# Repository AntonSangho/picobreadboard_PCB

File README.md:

# 프로젝트명 : 포르쉐 

### Images

# 요구사항 작성을 위한 질문 
- 수집하고자하는 환경데이터: 예) 온도, 습도  
- 휴대가능여부 
- 물리적인 사이즈 : 예) 휴대폰사이즈 , 카드지갑사이즈 
- 사용자가 손으로 제어하는 방식 : 예) 버튼
- 사용자가 동작을 확인하는 형태 : 예) LED, 부저음, 액정디스플레이
- 데이터를 확인하는 시각적인 결과물의 형태 : 예) 로우데이터, 그래프 
- 생각하는 키트의 외관 형태 
- 베터리로 동작하는 경우, 사용가능해야하는 대략적인 시간 
- 제작 수량

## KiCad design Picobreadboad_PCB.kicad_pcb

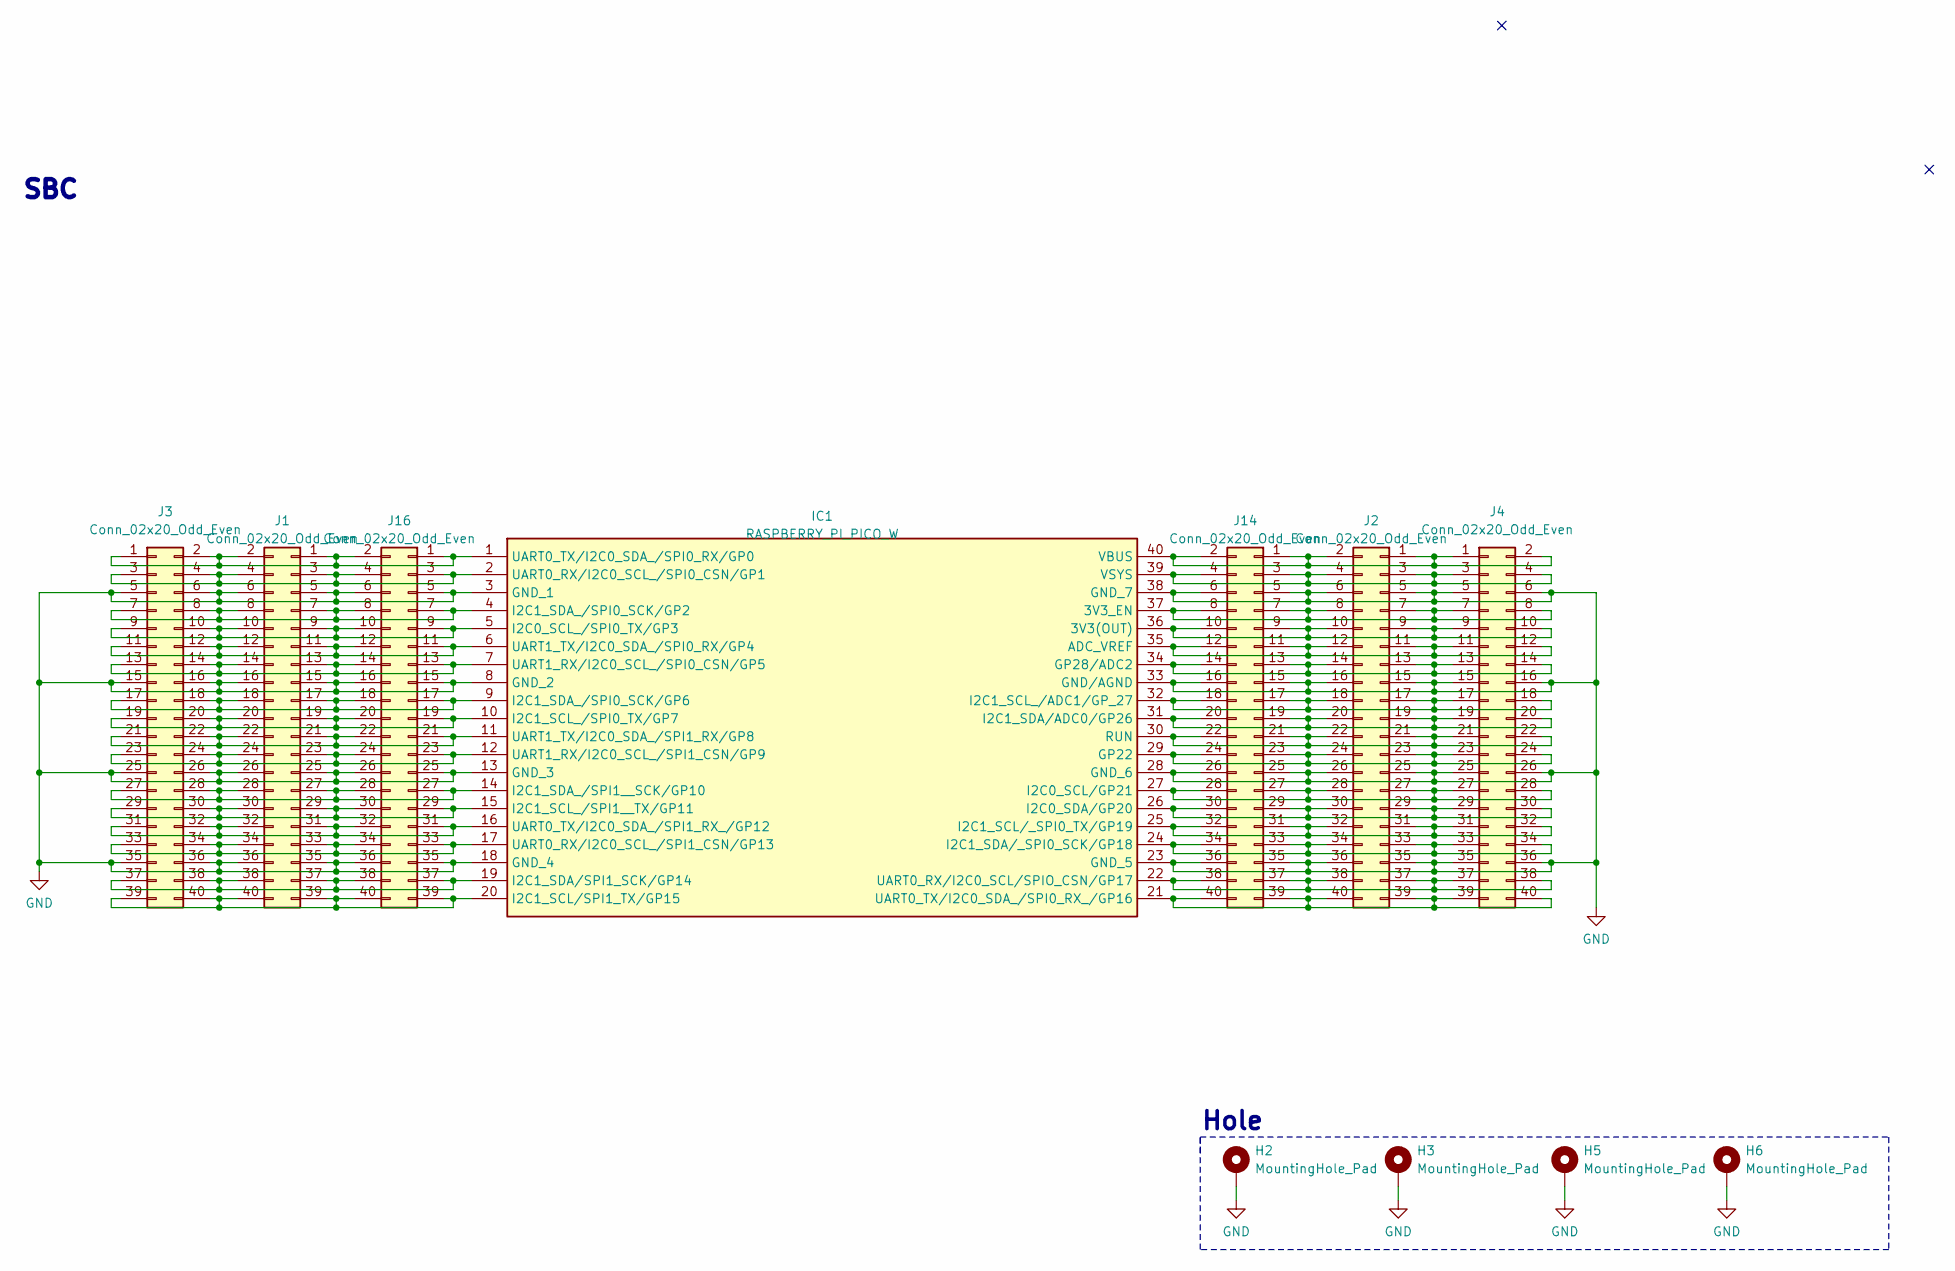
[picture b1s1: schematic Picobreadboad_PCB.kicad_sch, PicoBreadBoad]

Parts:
H2, H3, H5, H6: MountingHole_Pad; MountingHole_2.7mm_M2.5_ISO7380_Pad_TopOnly
IC1: RASPBERRY_PI_PICO_W; RASPBERRYPIPICOW; Manufacturer_Part_Number RASPBERRY PI PICO W
J1, J2, J14: Conn_02x20_Odd_Even; PinSocket_2x20_P2.54mm_Vertical_SMD; Mfr. Part # PM254-2-20-S-8.5; LCSC Part # C3975165
J3, J4: Conn_02x20_Odd_Even; PinHeader_2x20_P2.54mm_Vertical_SMD; Mfr. Part # HB-PH9-254220PB2GOP; LCSC Part # C6332245
J16: Conn_02x20_Odd_Even; PinSocket_2x20_P2.54mm_Vertical_SMD; LCSC Part # C3975165

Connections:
GND: H2.1, H3.1, H5.1, H6.1, IC1.3 (GND_1), IC1.8 (GND_2), IC1.13 (GND_3), IC1.18 (GND_4), IC1.23 (GND_5), IC1.28 (GND_6), IC1.33 (GND/AGND), IC1.38 (GND_7), J1.5, J1.6, J1.15, J1.16, J1.25, J1.26, J1.35, J1.36, J2.5, J2.6, J2.15, J2.16, J2.25, J2.26, J2.35, J2.36, J3.5, J3.6, J3.15, J3.16, J3.25, J3.26, J3.35, J3.36, J4.5, J4.6, J4.15, J4.16, J4.25, J4.26, J4.35, J4.36, J14.5, J14.6, J14.15, J14.16, J14.25, J14.26, J14.35, J14.36, J16.5, J16.6, J16.15, J16.16, J16.25, J16.26, J16.35, J16.36
unnamed: IC1.1 (UART0_TX/I2C0_SDA_/SPI0_RX/GP0), J1.1, J1.2, J3.1, J3.2, J16.1, J16.2
unnamed: IC1.2 (UART0_RX/I2C0_SCL_/SPI0_CSN/GP1), J1.3, J1.4, J3.3, J3.4, J16.3, J16.4
unnamed: IC1.4 (I2C1_SDA_/SPI0_SCK/GP2), J1.7, J1.8, J3.7, J3.8, J16.7, J16.8
unnamed: IC1.5 (I2C0_SCL_/SPI0_TX/GP3), J1.9, J1.10, J3.9, J3.10, J16.9, J16.10
unnamed: IC1.6 (UART1_TX/I2C0_SDA_/SPI0_RX/GP4), J1.11, J1.12, J3.11, J3.12, J16.11, J16.12
unnamed: IC1.7 (UART1_RX/I2C0_SCL_/SPI0_CSN/GP5), J1.13, J1.14, J3.13, J3.14, J16.13, J16.14
unnamed: IC1.9 (I2C1_SDA_/SPI0_SCK/GP6), J1.17, J1.18, J3.17, J3.18, J16.17, J16.18
unnamed: IC1.10 (I2C1_SCL_/SPI0_TX/GP7), J1.19, J1.20, J3.19, J3.20, J16.19, J16.20
unnamed: IC1.11 (UART1_TX/I2C0_SDA_/SPI1_RX/GP8), J1.21, J1.22, J3.21, J3.22, J16.21, J16.22
unnamed: IC1.12 (UART1_RX/I2C0_SCL_/SPI1_CSN/GP9), J1.23, J1.24, J3.23, J3.24, J16.23, J16.24
unnamed: IC1.14 (I2C1_SDA_/SPI1__SCK/GP10), J1.27, J1.28, J3.27, J3.28, J16.27, J16.28
unnamed: IC1.15 (I2C1_SCL_/SPI1__TX/GP11), J1.29, J1.30, J3.29, J3.30, J16.29, J16.30
unnamed: IC1.16 (UART0_TX/I2C0_SDA_/SPI1_RX_/GP12), J1.31, J1.32, J3.31, J3.32, J16.31, J16.32
unnamed: IC1.17 (UART0_RX/I2C0_SCL_/SPI1_CSN/GP13), J1.33, J1.34, J3.33, J3.34, J16.33, J16.34
unnamed: IC1.19 (I2C1_SDA/SPI1_SCK/GP14), J1.37, J1.38, J3.37, J3.38, J16.37, J16.38
unnamed: IC1.20 (I2C1_SCL/SPI1_TX/GP15), J1.39, J1.40, J3.39, J3.40, J16.39, J16.40
unnamed: IC1.40 (VBUS), J2.1, J2.2, J4.1, J4.2, J14.1, J14.2
unnamed: IC1.39 (VSYS), J2.3, J2.4, J4.3, J4.4, J14.3, J14.4
unnamed: IC1.37 (3V3_EN), J2.7, J2.8, J4.7, J4.8, J14.7, J14.8
unnamed: IC1.36 (3V3(OUT)), J2.9, J2.10, J4.9, J4.10, J14.9, J14.10
unnamed: IC1.35 (ADC_VREF), J2.11, J2.12, J4.11, J4.12, J14.11, J14.12
unnamed: IC1.34 (GP28/ADC2), J2.13, J2.14, J4.13, J4.14, J14.13, J14.14
unnamed: IC1.32 (I2C1_SCL_/ADC1/GP_27), J2.17, J2.18, J4.17, J4.18, J14.17, J14.18
unnamed: IC1.31 (I2C1_SDA/ADC0/GP26), J2.19, J2.20, J4.19, J4.20, J14.19, J14.20
unnamed: IC1.30 (RUN), J2.21, J2.22, J4.21, J4.22, J14.21, J14.22
unnamed: IC1.29 (GP22), J2.23, J2.24, J4.23, J4.24, J14.23, J14.24
unnamed: IC1.27 (I2C0_SCL/GP21), J2.27, J2.28, J4.27, J4.28, J14.27, J14.28
unnamed: IC1.26 (I2C0_SDA/GP20), J2.29, J2.30, J4.29, J4.30, J14.29, J14.30
unnamed: IC1.25 (I2C1_SCL/_SPI0_TX/GP19), J2.31, J2.32, J4.31, J4.32, J14.31, J14.32
unnamed: IC1.24 (I2C1_SDA/_SPI0_SCK/GP18), J2.33, J2.34, J4.33, J4.34, J14.33, J14.34
unnamed: IC1.22 (UART0_RX/I2C0_SCL/SPIO_CSN/GP17), J2.37, J2.38, J4.37, J4.38, J14.37, J14.38
unnamed: IC1.21 (UART0_TX/I2C0_SDA_/SPI0_RX_/GP16), J2.39, J2.40, J4.39, J4.40, J14.39, J14.40

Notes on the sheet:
Hole
SBC

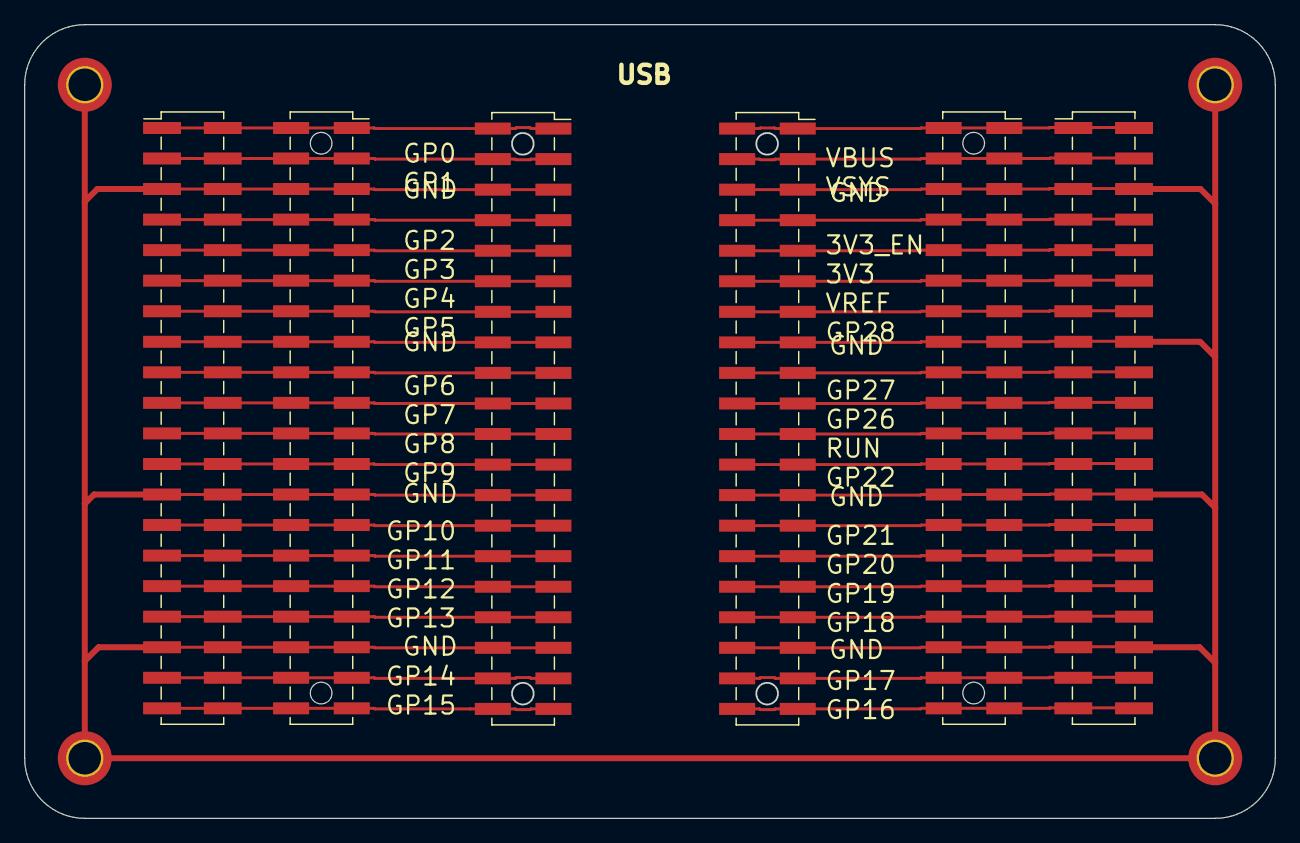
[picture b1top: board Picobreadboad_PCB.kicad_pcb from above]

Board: 2 copper layers, 104.0 x 66.0 mm, 10 parts (0 on the bottom side), 33 nets.

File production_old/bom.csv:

Designator,Footprint,Quantity,Value,LCSC Part #,Mfr. Part #
"J1, J14, J16, J2",PinSocket_2x20_P2.54mm_Vertical_SMD,4,Conn_02x20_Odd_Even,C3975165,PM254-2-20-S-8.5
"J3, J4",PinHeader_2x20_P2.54mm_Vertical_SMD,2,Conn_02x20_Odd_Even,C6332245,HB-PH9-254220PB2GOP

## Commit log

2024-06-14 add kicad project
2024-06-24 kicadfile
